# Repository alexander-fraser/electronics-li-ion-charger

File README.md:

# electronics-li-ion-charger
A general-purpose li-ion battery charger board based on the MCP73831 IC. Can charge only a single cell (3.7V). 

Issue Log:
- Reverse polarity protection does not function as intended (i.e. it doesn't work).

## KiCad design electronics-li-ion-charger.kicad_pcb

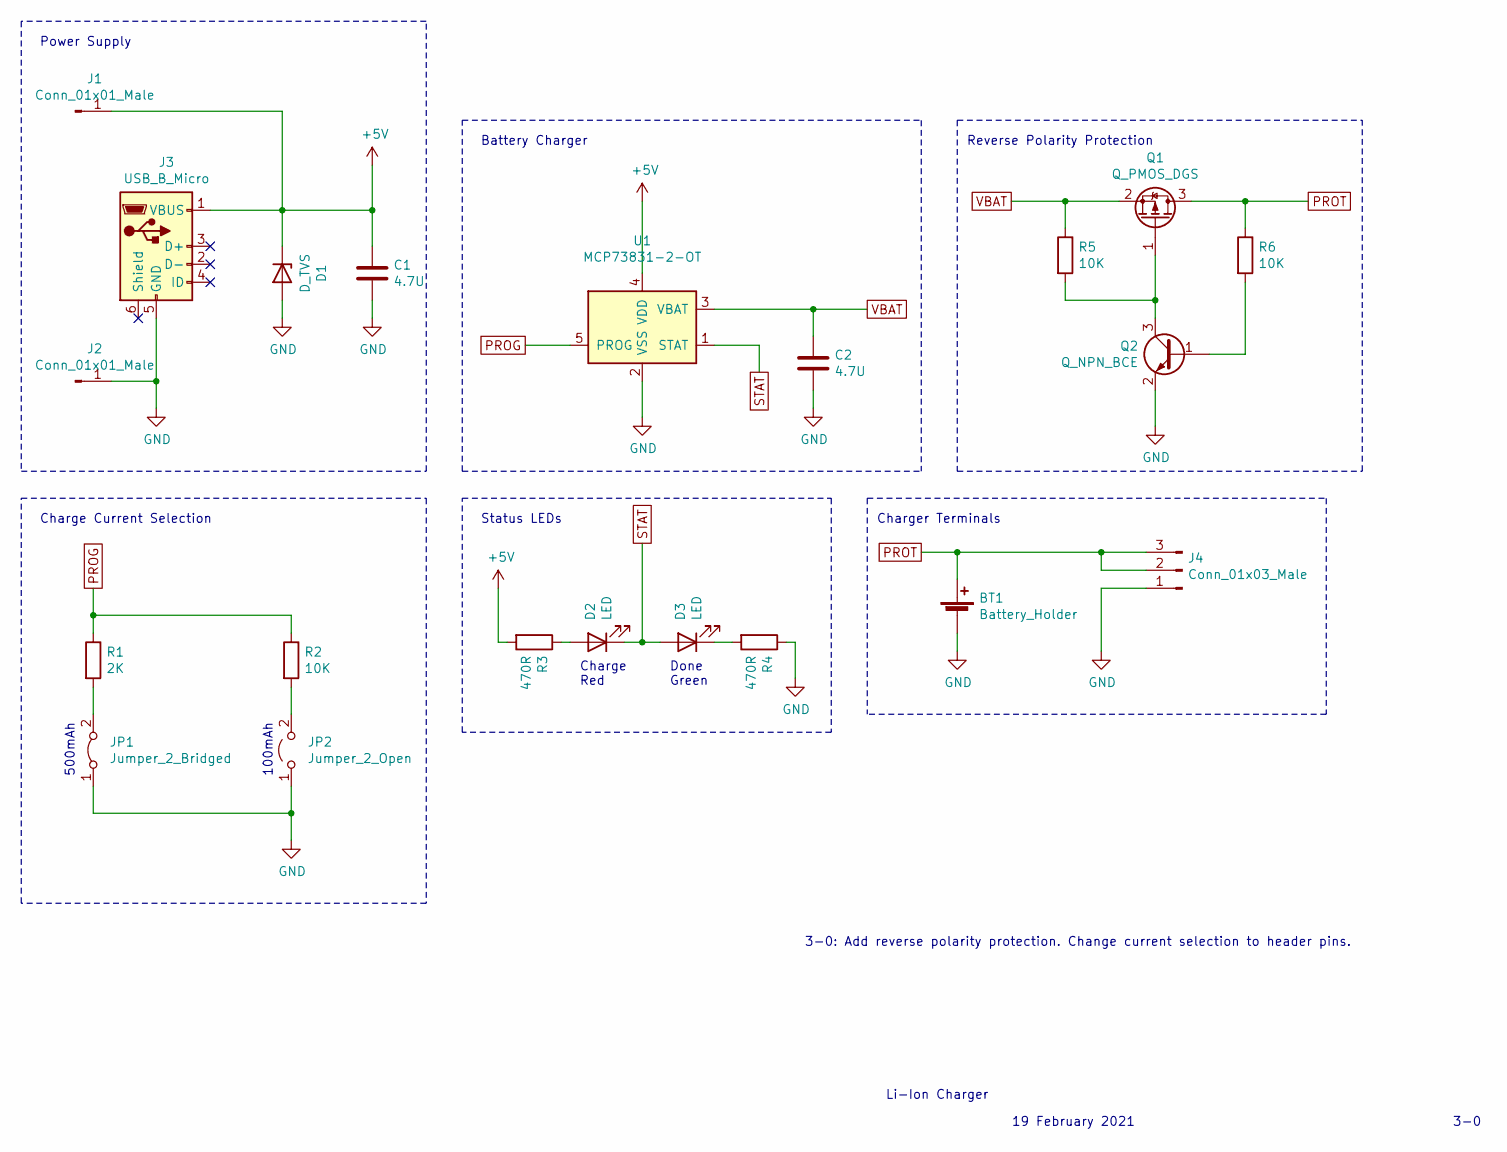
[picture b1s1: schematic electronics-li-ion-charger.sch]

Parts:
BT1: Battery_Holder; Battery_Holder-PC_Pin-18650
C1, C2: 4.7U; C_1206_3216Metric_Pad1.33x1.80mm_HandSolder
D1: D_TVS; Diode_TVS-MSP5.0A
D2, D3: LED; LED_1206_3216Metric_Pad1.42x1.75mm_HandSolder
J1, J2: Conn_01x01_Male; PinHeader_1x01_P2.54mm_Vertical
J3: USB_B_Micro; USB_Micro-B_Amphenol_10118194_Horizontal
J4: Conn_01x03_Male; PinHeader_1x03_P2.54mm_Vertical
JP1: Jumper_2_Bridged; PinHeader_1x02_P2.54mm_Vertical
JP2: Jumper_2_Open; PinHeader_1x02_P2.54mm_Vertical
Q1: Q_PMOS_DGS; SOT-23_Handsoldering
Q2: Q_NPN_BCE; SOT-23_Handsoldering
R1: 2K; R_1206_3216Metric_Pad1.30x1.75mm_HandSolder
R2, R5, R6: 10K; R_1206_3216Metric_Pad1.30x1.75mm_HandSolder
R3, R4: 470R; R_1206_3216Metric_Pad1.30x1.75mm_HandSolder
U1: MCP73831-2-OT; SOT-23-5_HandSoldering

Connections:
+5V: C1.1, D1.1 (K), J1.1, J3.1 (VBUS), R3.2, U1.4 (VDD)
GND: BT1.2 (-), C1.2, C2.2, D1.2 (A), J2.1, J3.5 (GND), J4.1, JP1.1 (A), JP2.1 (A), Q2.2 (E), R4.1, U1.2 (VSS)
unnamed: D2.2 (A), R3.1
unnamed: D3.1 (K), R4.2
unnamed: JP1.2 (B), R1.2
unnamed: JP2.2 (B), R2.2
unnamed: Q1.1 (G), Q2.3 (C), R5.2
unnamed: Q2.1 (B), R6.2
PROG: R1.1, R2.1, U1.5 (PROG)
PROT: BT1.1 (+), J4.2, J4.3, Q1.3 (D), R6.1
STAT: D2.1 (K), D3.2 (A), U1.1 (STAT)
VBAT: C2.1, Q1.2 (S), R5.1, U1.3 (VBAT)

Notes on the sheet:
Power Supply
Charge Current Selection
500mAh
100mAh
Status LEDs
Charge Red
Done Green
Battery Charger
19 February 2021
3-0
Li-Ion Charger
3-0: Add reverse polarity protection. Change current selection to header pins.
Reverse Polarity Protection
Charger Terminals

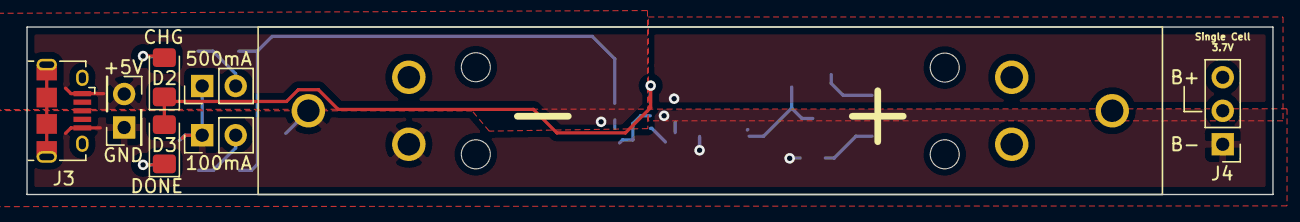
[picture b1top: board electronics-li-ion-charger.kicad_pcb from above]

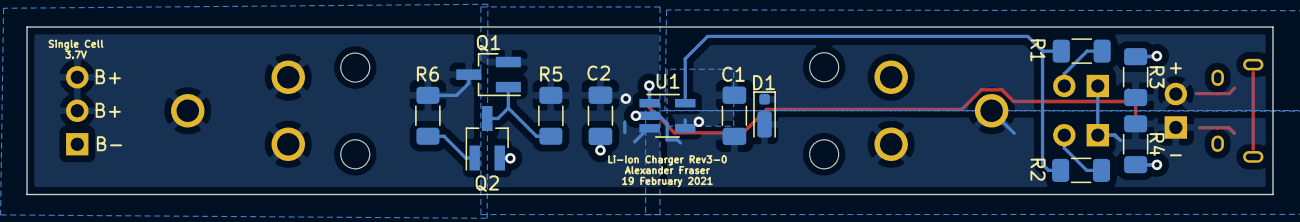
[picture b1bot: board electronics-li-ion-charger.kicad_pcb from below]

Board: 2 copper layers, 94.5 x 12.7 mm, 25 parts (12 on the bottom side), 12 nets.

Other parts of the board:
M1, M2, M3, M4: MountingHole_2.2mm_M2

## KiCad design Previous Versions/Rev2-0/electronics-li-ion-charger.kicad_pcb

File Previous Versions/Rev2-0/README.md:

# electronics-li-ion-charger
A general-purpose li-ion battery charger board based on the MCP73831 IC. Can charge only a single cell (3.7V). 

Issue log:
- Status LEDs are shorted!
- PROG circuit is left floating (via is misaligned), so charger does not start.

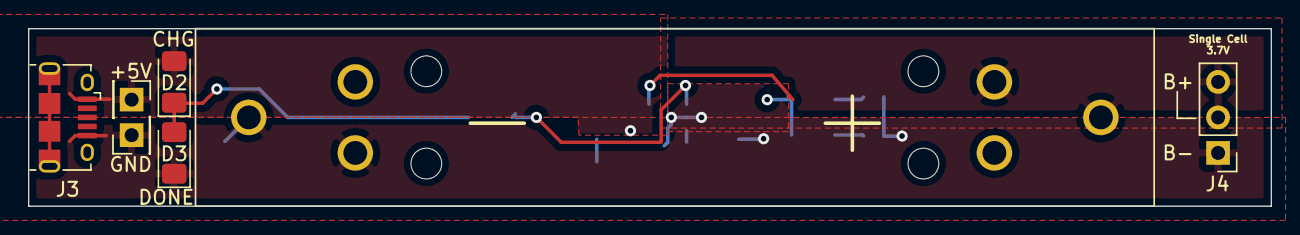
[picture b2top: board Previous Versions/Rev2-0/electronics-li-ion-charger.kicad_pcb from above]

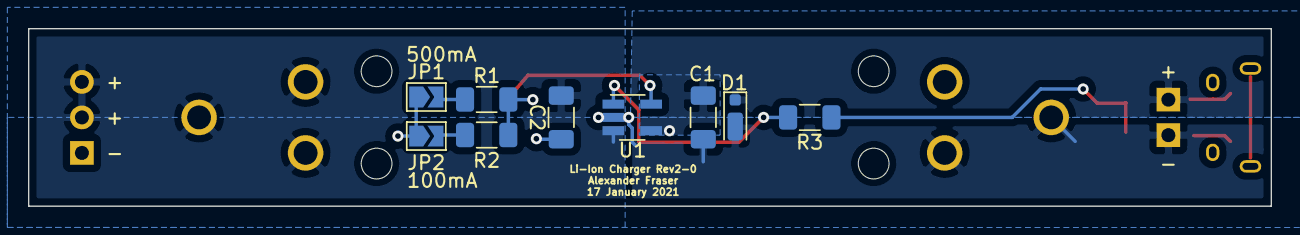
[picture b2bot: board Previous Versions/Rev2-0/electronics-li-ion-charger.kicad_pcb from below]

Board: 2 copper layers, 88.9 x 12.7 mm, 20 parts (9 on the bottom side), 8 nets.

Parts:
BT1: Battery_Holder; Battery_Holder-PC_Pin-18650
C1, C2: 4.7U; C_1206_3216Metric_Pad1.33x1.80mm_HandSolder
D1: D_TVS; Diode_TVS-MSP5.0A
D2, D3: LED; LED_1206_3216Metric_Pad1.42x1.75mm_HandSolder
J1, J2: Conn_01x01_Male; PinHeader_1x01_P2.54mm_Vertical
J3: USB_B_Micro; USB_Micro-B_Amphenol_10118194_Horizontal
J4: Conn_01x03_Male; PinHeader_1x03_P2.54mm_Vertical
JP1: Jumper_2_Bridged; SolderJumper-2_P1.3mm_Open_TrianglePad1.0x1.5mm
JP2: Jumper_2_Open; SolderJumper-2_P1.3mm_Open_TrianglePad1.0x1.5mm
M1, M2, M3, M4: MountingHole_2.2mm_M2
R1: 2K; R_1206_3216Metric_Pad1.30x1.75mm_HandSolder
R2: 10K; R_1206_3216Metric_Pad1.30x1.75mm_HandSolder
R3: 470R; R_1206_3216Metric_Pad1.30x1.75mm_HandSolder
U1: MCP73831-2-OT; SOT-23-5_HandSoldering

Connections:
+5V: C1.1, D1.1, D2.2, J1.1, J3.1, U1.4
/VBAT: BT1.1, C2.1, J4.2, J4.3, U1.3
GND: BT1.2, C1.2, C2.2, D1.2, D3.1, J2.1, J3.5, J4.1, JP1.1, JP2.1, U1.2
unnamed: D2.1, D3.2, R3.2
unnamed: JP1.2, R1.2
unnamed: JP2.2, R2.2
PROG: R1.1, R2.1, U1.5
STAT: R3.1, U1.1

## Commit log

2021-01-10 Initialize KiCad project.
2021-01-10 Re-initialize KiCad project.
2021-01-10 Draft schematic.
2021-01-15 Complete charge current selection schematic.
2021-01-15 Complete status LED schematic.
2021-01-15 Complete schematic.
2021-01-15 Create and assign TVS diode layout.
2021-01-16 Draft PCB layout.
2021-01-16 Place components in PCB layout.
2021-01-16 Add traces to PCB layout.
2021-01-16 Add power planes.
2021-01-16 Add silkscreen text.
2021-01-16 Reverse polarity of TVS diode layout.
2021-01-16 Run DRC and clean copper planes.
2021-01-16 Generate Gerbers and plots.
2021-01-16 Modify silk screen text.
2021-01-16 Archive Rev1-0 and start Rev2-0.
2021-01-16 Add 18650 holder to schematic.
2021-01-17 Layout PCB with 18650 battery holder.
2021-01-17 Modify layout with 18650 holder and fix silkscreen.
2021-01-17 Generate plots.
2021-02-13 Log issues with Rev2-0
2021-02-14 Rev2-1: Fix LED short circuit and PROG trace.
2021-02-20 Archive rev 2-1.
2021-02-20 Rev3-0: Add reverse polarity protection.
